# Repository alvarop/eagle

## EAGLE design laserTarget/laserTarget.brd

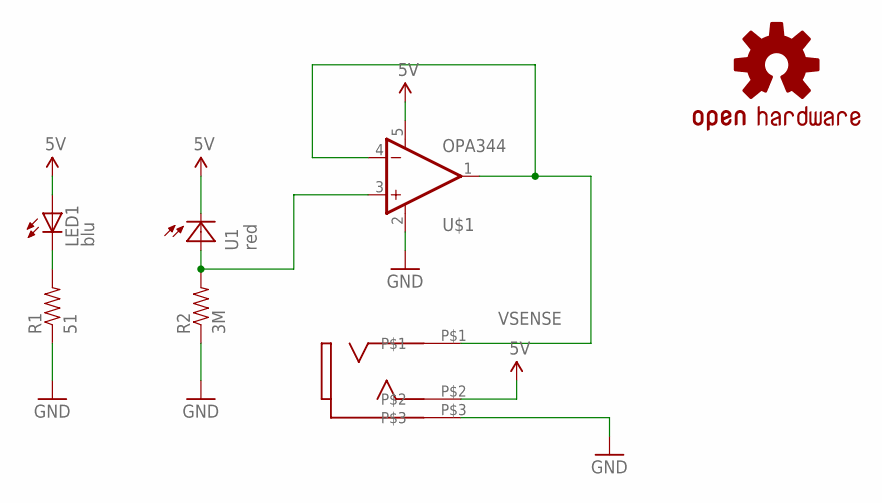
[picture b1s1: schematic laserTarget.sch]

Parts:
LED1: blu; LED5MM
LOGO1: OSHW-LOGOS; OSHW-LOGO-S
R1: 51; 0805
R2: 3M; 0805
U1: red; CLS15
U$1: OPA344; SOT23-5
U$2: 35RASMT2BHNTRX

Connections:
5V: LED1.A, U1.3 (C), U1.4 (C), U$1.5 (V+), U$2.P$2
GND: R1.1, R2.1, U$1.2 (V-), U$2.P$3
unnamed: R2.2, U1.1 (A), U1.2 (A), U$1.3 (+IN)
unnamed: LED1.K (C), R1.2
VSENSE: U$1.1 (OUT), U$1.4 (-IN), U$2.P$1

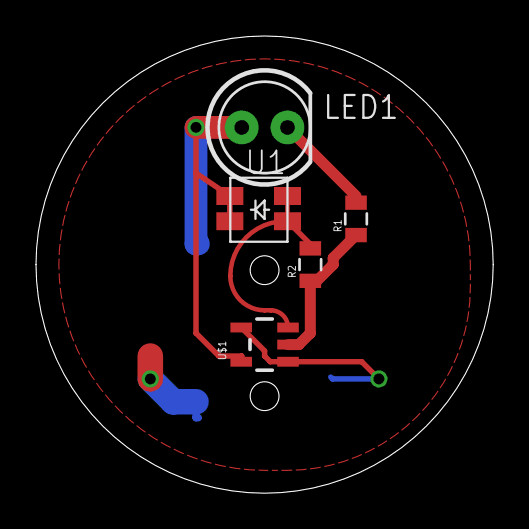
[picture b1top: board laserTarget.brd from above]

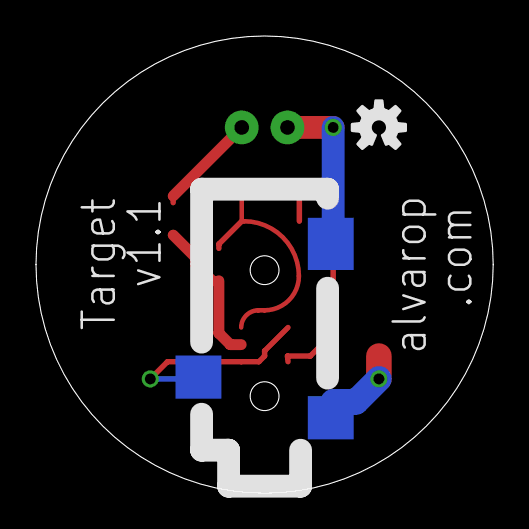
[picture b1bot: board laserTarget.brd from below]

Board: 2 copper layers, 25.4 x 25.4 mm, 7 parts (2 on the bottom side), 5 nets.

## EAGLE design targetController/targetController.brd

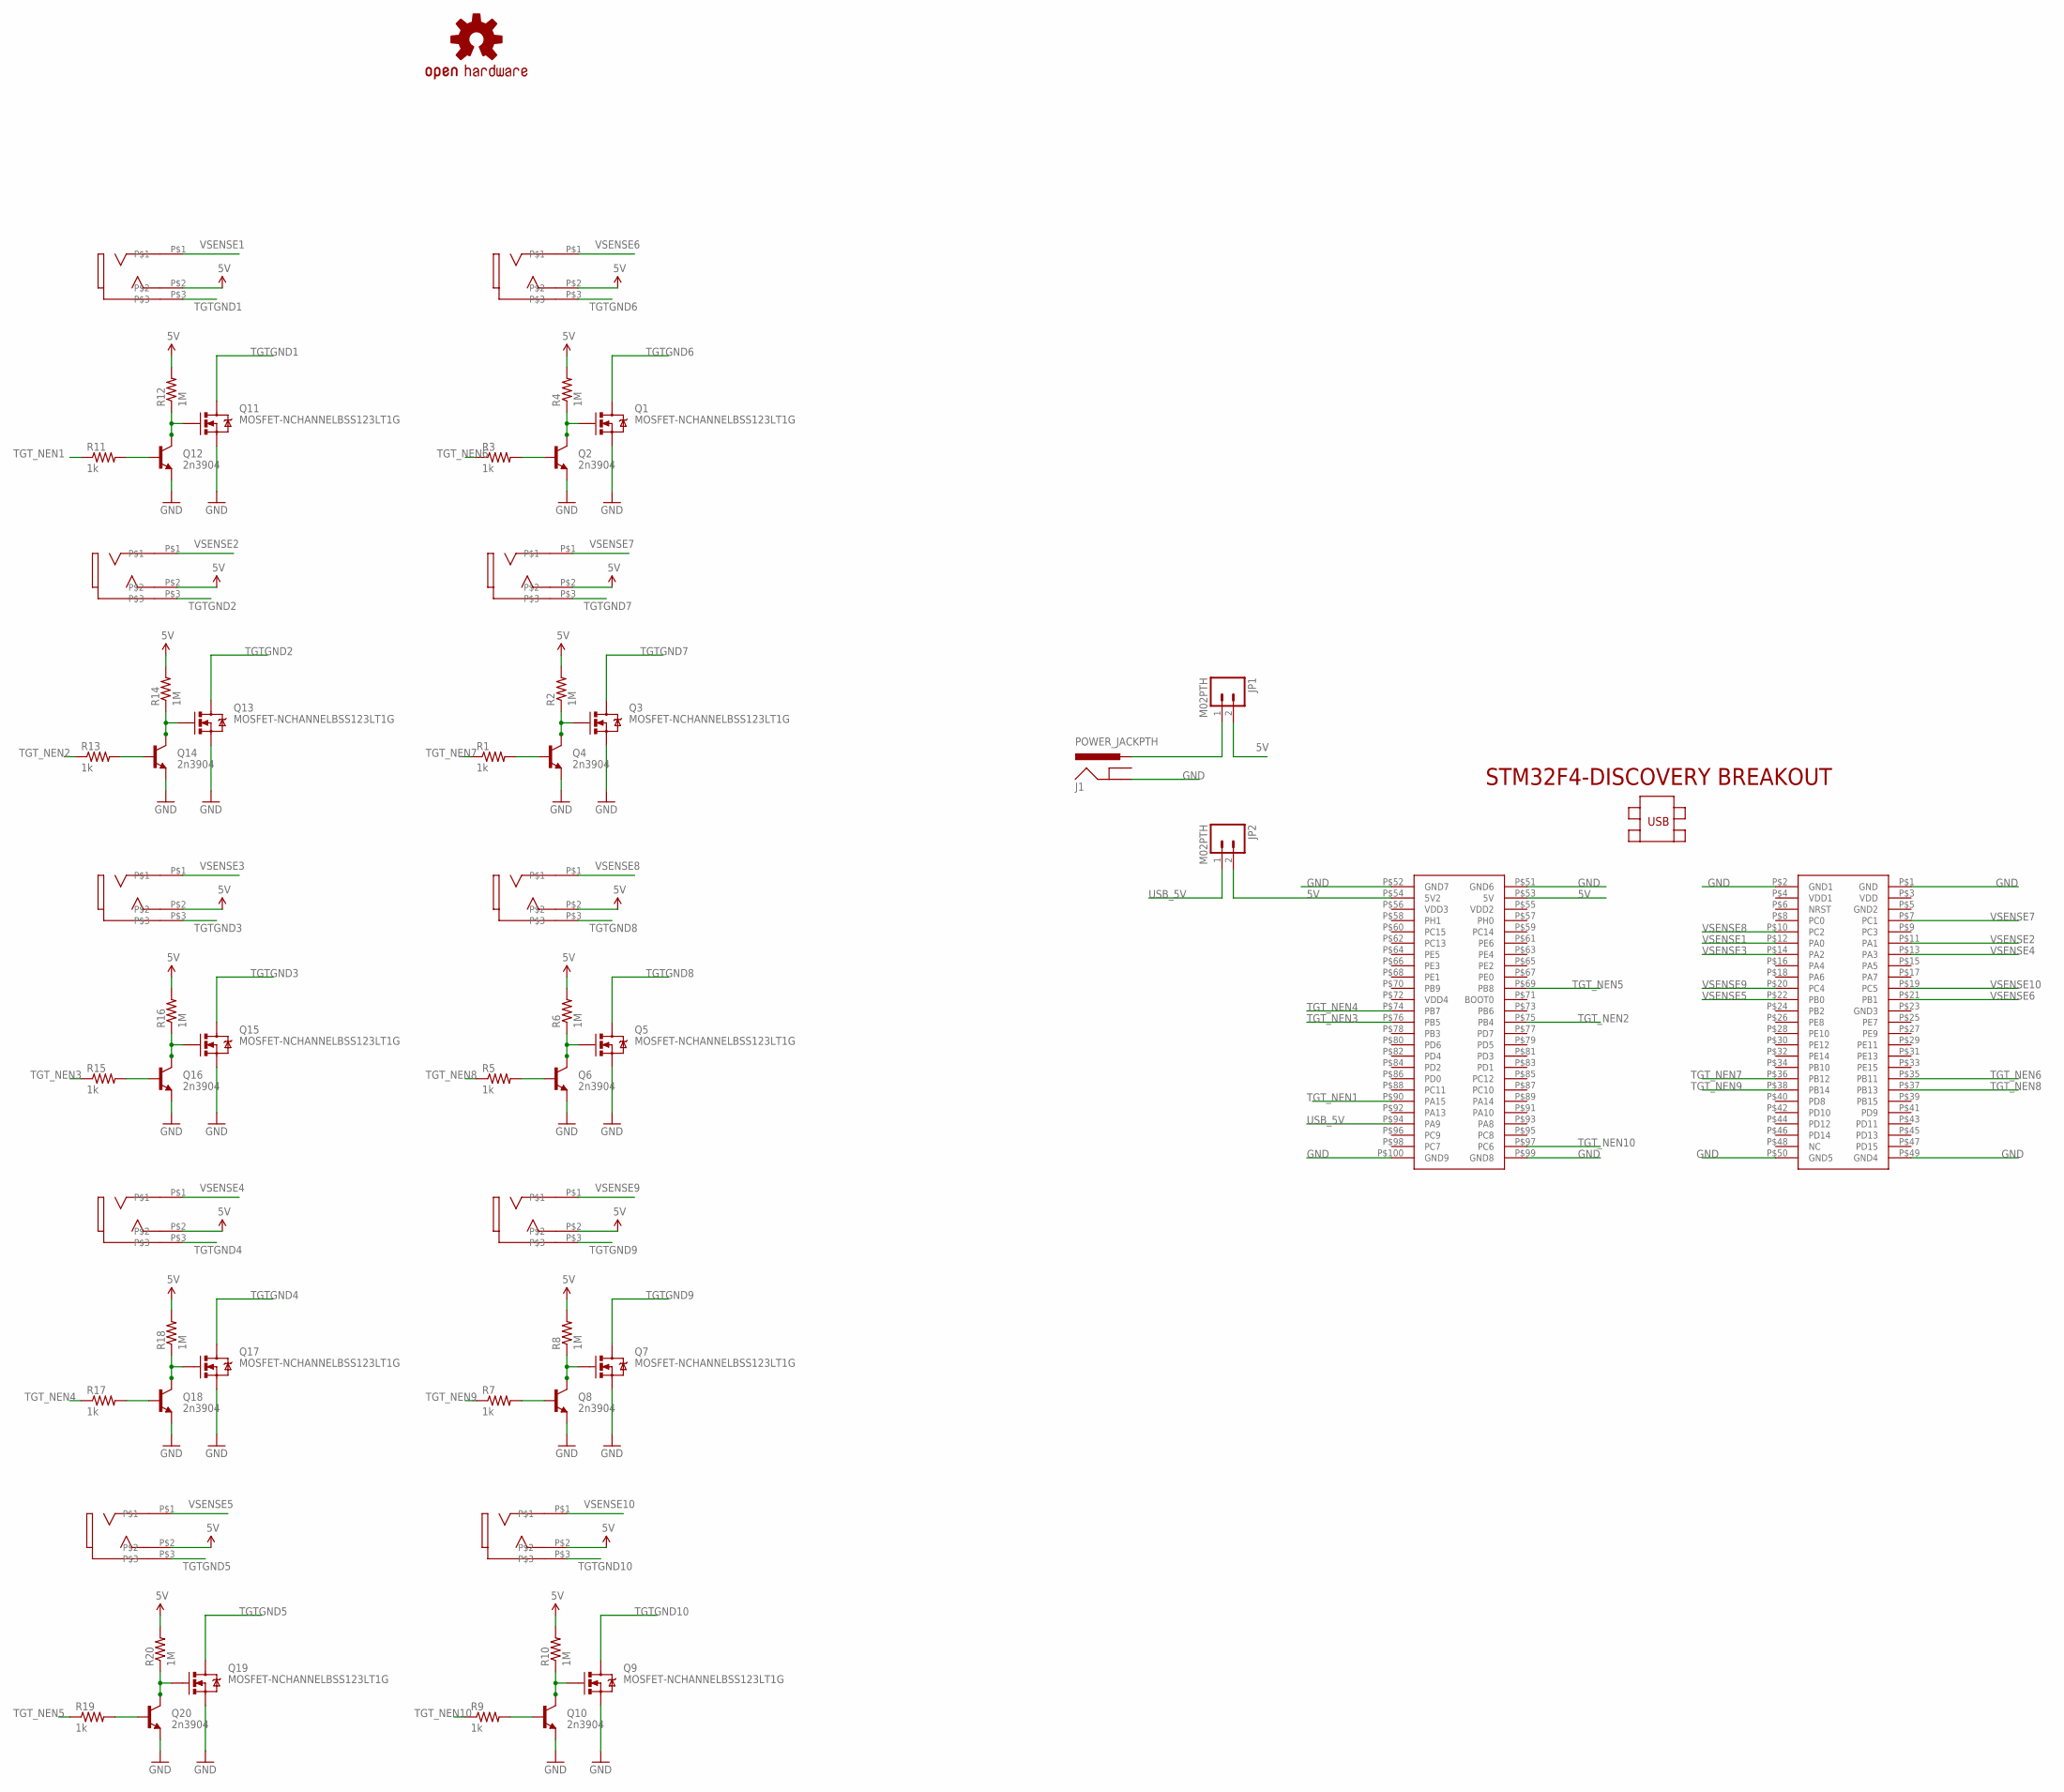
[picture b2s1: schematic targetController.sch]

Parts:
J1: POWER_JACKPTH; POWER_JACK_PTH
JP1, JP2: M02PTH; 1X02
LOGO1: OSHW-LOGOS; OSHW-LOGO-S
Q1, Q3, Q5, Q7, Q9, Q11, Q13, Q15, Q17, Q19: MOSFET-NCHANNELBSS123LT1G; SOT23
Q2, Q4, Q6, Q8, Q10, Q12, Q14, Q16, Q18, Q20: 2n3904; SOT23-3
R1, R3, R5, R7, R9, R11, R13, R15, R17, R19: 1k; 0805
R2, R4, R6, R8, R10, R12, R14, R16, R18, R20: 1M; 0805
T1, T2, T3, T4, T5, T6, T7, T8, T9, T10: 35RASMT2BHNTRX
U$1: STM32F4-DISCOVERY

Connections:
5V: JP1.2, JP2.2, R2.2, R4.2, R6.2, R8.2, R10.2, R12.2, R14.2, R16.2, R18.2, R20.2, T1.P$2, T2.P$2, T3.P$2, T4.P$2, T5.P$2, T6.P$2, T7.P$2, T8.P$2, T9.P$2, T10.P$2, U$1.P$53 (5V), U$1.P$54 (5V2)
GND: J1.GND, Q1.2 (S), Q2.2 (E), Q3.2 (S), Q4.2 (E), Q5.2 (S), Q6.2 (E), Q7.2 (S), Q8.2 (E), Q9.2 (S), Q10.2 (E), Q11.2 (S), Q12.2 (E), Q13.2 (S), Q14.2 (E), Q15.2 (S), Q16.2 (E), Q17.2 (S), Q18.2 (E), Q19.2 (S), Q20.2 (E), U$1.P$1 (GND), U$1.P$2 (GND1), U$1.P$49 (GND4), U$1.P$50 (GND5), U$1.P$51 (GND6), U$1.P$52 (GND7), U$1.P$99 (GND8), U$1.P$100 (GND9)
N1: Q3.1 (G), Q4.3 (C), R2.1
N2: Q5.1 (G), Q6.3 (C), R6.1
N3: Q1.1 (G), Q2.3 (C), R4.1
N4: Q7.1 (G), Q8.3 (C), R8.1
N5: Q9.1 (G), Q10.3 (C), R10.1
N6: Q11.1 (G), Q12.3 (C), R12.1
N7: Q13.1 (G), Q14.3 (C), R14.1
N8: Q15.1 (G), Q16.3 (C), R16.1
N9: Q17.1 (G), Q18.3 (C), R18.1
N10: Q19.1 (G), Q20.3 (C), R20.1
unnamed: Q4.1 (B), R1.2
unnamed: J1.PWR, JP1.1
unnamed: Q2.1 (B), R3.2
unnamed: Q6.1 (B), R5.2
unnamed: Q8.1 (B), R7.2
unnamed: Q10.1 (B), R9.2
unnamed: Q12.1 (B), R11.2
unnamed: Q14.1 (B), R13.2
unnamed: Q16.1 (B), R15.2
unnamed: Q18.1 (B), R17.2
unnamed: Q20.1 (B), R19.2
TGTGND1: Q11.3 (D), T1.P$3
TGTGND2: Q13.3 (D), T2.P$3
TGTGND3: Q15.3 (D), T3.P$3
TGTGND4: Q17.3 (D), T4.P$3
TGTGND5: Q19.3 (D), T5.P$3
TGTGND6: Q1.3 (D), T6.P$3
TGTGND7: Q3.3 (D), T7.P$3
TGTGND8: Q5.3 (D), T8.P$3
TGTGND9: Q7.3 (D), T9.P$3
TGTGND10: Q9.3 (D), T10.P$3
TGT_NEN1: R11.1, U$1.P$90 (PA15)
TGT_NEN2: R13.1, U$1.P$75 (PB4)
TGT_NEN3: R15.1, U$1.P$76 (PB5)
TGT_NEN4: R17.1, U$1.P$74 (PB7)
TGT_NEN5: R19.1, U$1.P$69 (PB8)
TGT_NEN6: R3.1, U$1.P$35 (PB11)
TGT_NEN7: R1.1, U$1.P$36 (PB12)
TGT_NEN8: R5.1, U$1.P$37 (PB13)
TGT_NEN9: R7.1, U$1.P$38 (PB14)
TGT_NEN10: R9.1, U$1.P$97 (PC6)
USB_5V: JP2.1, U$1.P$94 (PA9)
VSENSE1: T1.P$1, U$1.P$12 (PA0)
VSENSE2: T2.P$1, U$1.P$11 (PA1)
VSENSE3: T3.P$1, U$1.P$14 (PA2)
VSENSE4: T4.P$1, U$1.P$13 (PA3)
VSENSE5: T5.P$1, U$1.P$22 (PB0)
VSENSE6: T6.P$1, U$1.P$21 (PB1)
VSENSE7: T7.P$1, U$1.P$7 (PC1)
VSENSE8: T8.P$1, U$1.P$10 (PC2)
VSENSE9: T9.P$1, U$1.P$20 (PC4)
VSENSE10: T10.P$1, U$1.P$19 (PC5)

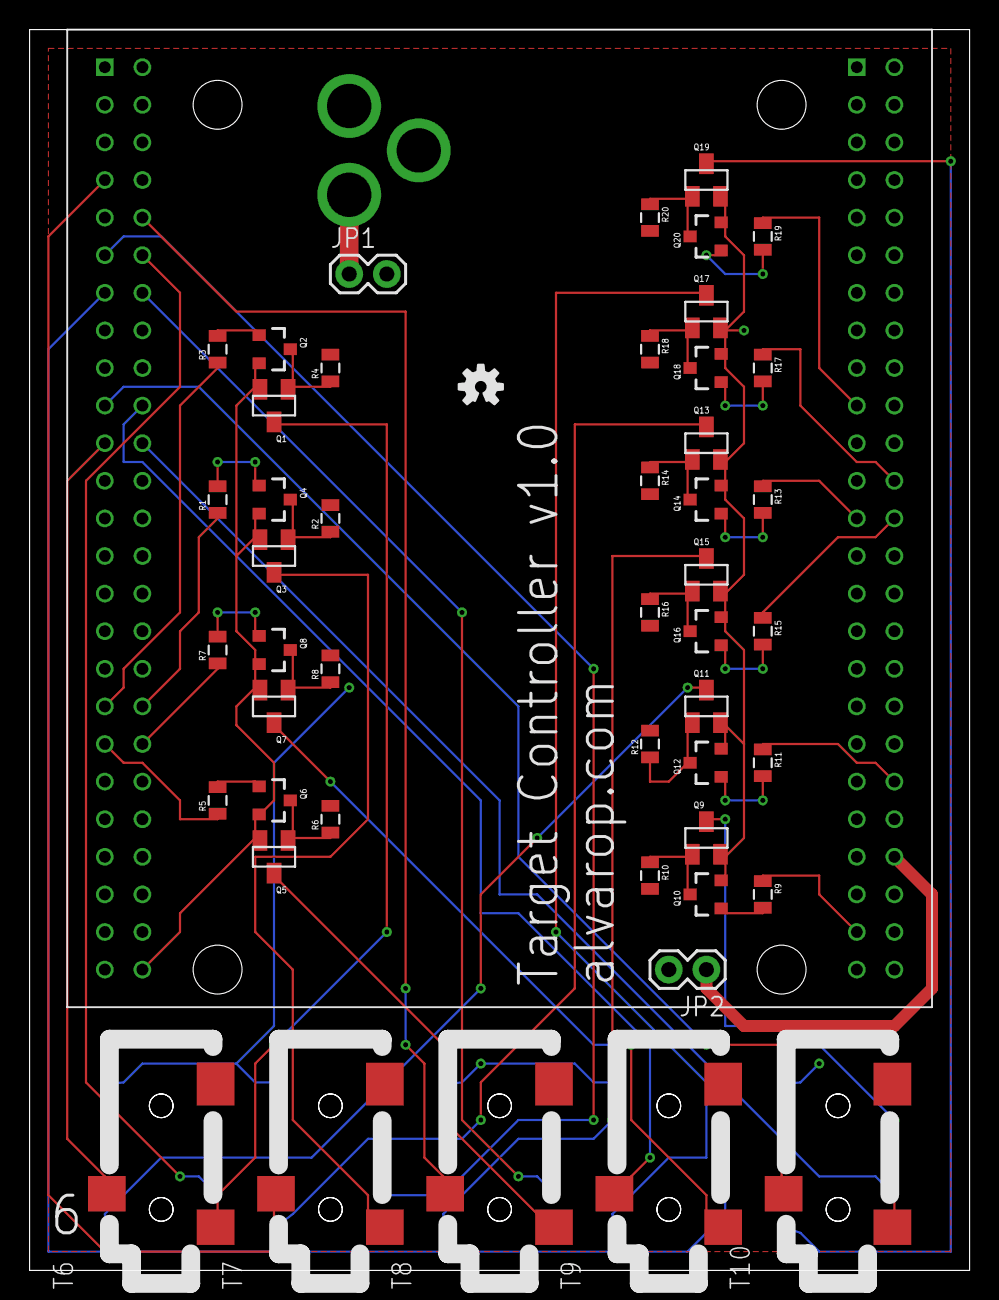
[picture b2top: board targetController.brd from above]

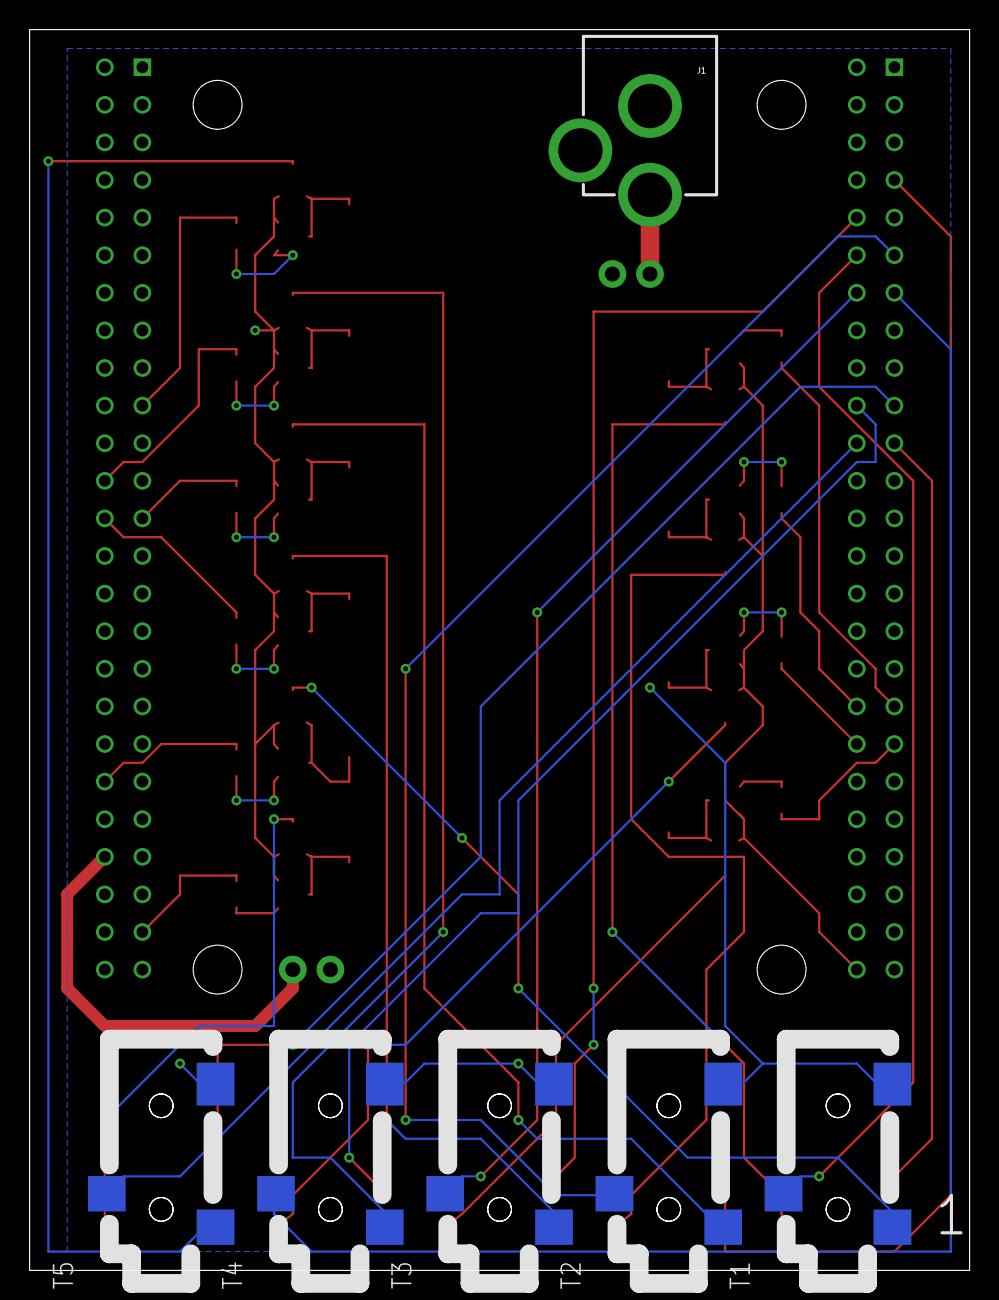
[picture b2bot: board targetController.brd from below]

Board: 2 copper layers, 63.5 x 83.8 mm, 59 parts (6 on the bottom side), 54 nets.

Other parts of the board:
U$2, U$3, U$4, U$5: STAND-OFF

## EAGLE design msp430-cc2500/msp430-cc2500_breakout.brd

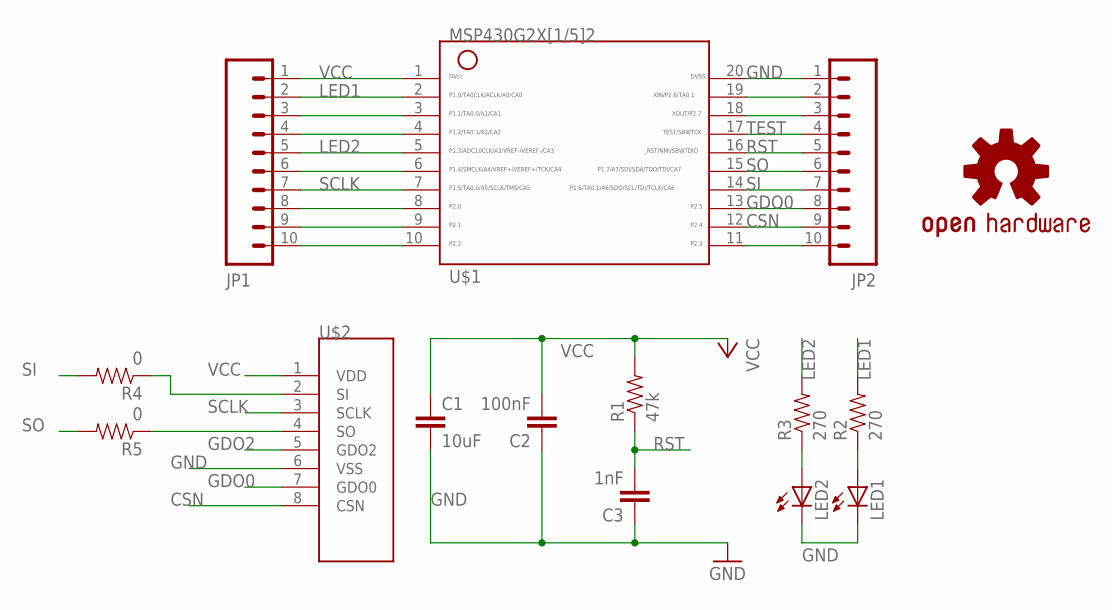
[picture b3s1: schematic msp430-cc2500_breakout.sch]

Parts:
C1: 10uF; 0805
C2: 100nF; 0805
C3: 1nF; 0805
JP1, JP2: M10"; 1X10
LED1, LED2: LED1206; LED-1206
R1: 47k; 0805
R2, R3: 270; 0805
R4, R5: 0; 0805
U$1: G2X[1/5]2---PW20; PW20
U$2: CC2500-MODULESMT; CC2500-MODULE-SMT
U$3: OSHW-LOGOL; OSHW-LOGO-L

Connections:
CSN: JP2.9, U$1.12, U$2.8 (CSN)
GDO0: JP2.8, U$1.13, U$2.7 (GDO0)
GDO2: U$2.5 (GDO2)
GND: C1.2, C2.1, C3.1, JP2.1, LED1.C, LED2.C, U$1.20, U$2.6 (VSS)
LED1: JP1.2, R2.2, U$1.2
LED2: JP1.5, R3.2, U$1.5
unnamed: LED1.A, R2.1
unnamed: JP1.3, U$1.3
unnamed: JP1.4, U$1.4
unnamed: JP1.6, U$1.6
unnamed: LED2.A, R3.1
unnamed: JP1.8, U$1.8
unnamed: JP1.9, U$1.9
unnamed: JP1.10, U$1.10
unnamed: JP2.2, U$1.19
unnamed: JP2.3, U$1.18
unnamed: JP2.10, U$1.11
unnamed: R4.1, U$2.2 (SI)
unnamed: R5.1, U$2.4 (SO)
RST: C3.2, JP2.5, R1.1, U$1.16
SCLK: JP1.7, U$1.7, U$2.3 (SCLK)
SI: JP2.7, R4.2, U$1.14
SO: JP2.6, R5.2, U$1.15
TEST: JP2.4, U$1.17
VCC: C1.1, C2.2, JP1.1, R1.2, U$1.1, U$2.1 (VDD)

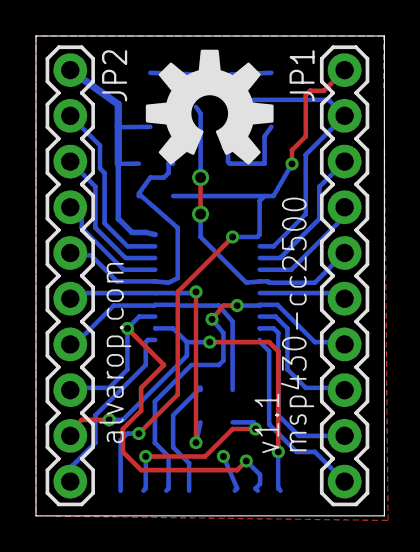
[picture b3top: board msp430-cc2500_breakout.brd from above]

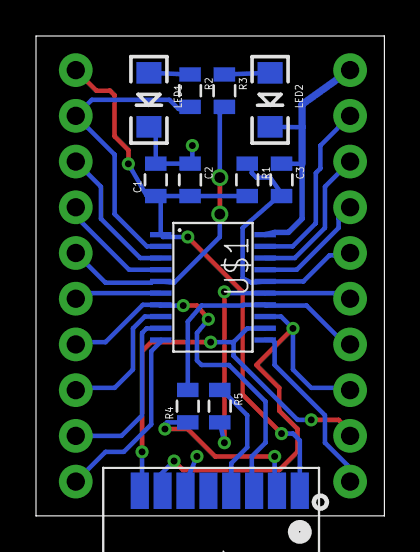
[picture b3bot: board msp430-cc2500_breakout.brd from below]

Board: 2 copper layers, 19.4 x 26.7 mm, 15 parts (12 on the bottom side), 24 nets.

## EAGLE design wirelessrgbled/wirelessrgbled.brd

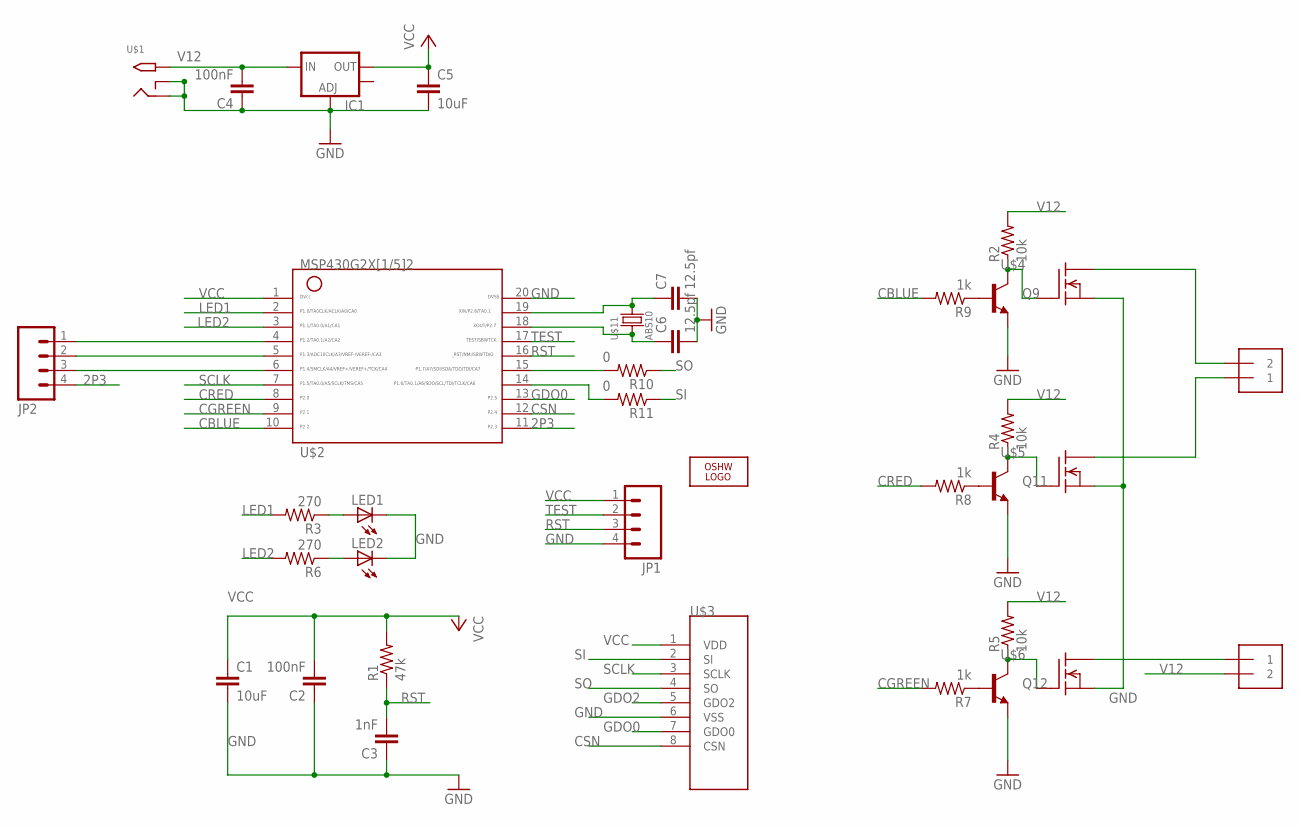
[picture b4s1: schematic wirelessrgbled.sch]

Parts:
C1, C5: 10uF; 0805
C2, C4: 100nF; 0805
C3: 1nF; 0805
C6, C7: 12.5pf; 0805
IC1: V_REG_LM1117SOT223; SOT223
J1, J2: 1X2-3.5MM
JP1, JP2: M04PTH; 1X04
LED1, LED2: LEDCHIPLED_0805; CHIPLED_0805
LOGO1: OSHW_LOGO_10MILX0200-NT; OSHW_10X200_NOTEXT
Q9, Q11, Q12: TRANSISTOR_NPNSOT23; SOT23
R1: 47k; 0805
R2, R4, R5: 10k; 0805
R3, R6: 270; 0805
R7, R8, R9: 1k; 0805
R10, R11: 0; 0805
U$1: 2.1MMJACKTHM; PJ-102A
U$2: G2X[1/5]2---PW20; PW20
U$3: CC2500-MODULE
U$4, U$5, U$6: BUK92150; TO252
U$11: ABS10

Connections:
2P3: JP2.4, U$2.11
CBLUE: R9.2, U$2.10
CGREEN: R7.2, U$2.9
CRED: R8.2, U$2.8
CSN: U$2.12, U$3.8 (CSN)
GDO0: U$2.13, U$3.7 (GDO0)
GDO2: U$3.5 (GDO2)
GND: C1.2, C2.1, C3.1, C4.1, C5.2, C6.2, C7.2, IC1.1 (ADJ), JP1.4, LED1.C, LED2.C, Q9.2 (E), Q11.2 (E), Q12.2 (E), U$1.RING, U$1.RING_SW, U$2.20, U$3.6 (VSS), U$4.3 (S), U$5.3 (S), U$6.3 (S)
LED1: R3.2, U$2.2
LED2: R6.2, U$2.3
unnamed: JP2.2, U$2.5
unnamed: Q9.3 (C), R2.1, U$4.1 (G)
unnamed: LED1.A, R3.1
unnamed: J2.1, U$6.2 (D)
unnamed: J1.2, U$4.2 (D)
unnamed: J1.1, U$5.2 (D)
unnamed: R10.2, U$2.15
unnamed: LED2.A, R6.1
unnamed: R11.2, U$2.14
unnamed: Q11.3 (C), R4.1, U$5.1 (G)
unnamed: Q9.1 (B), R9.1
unnamed: Q11.1 (B), R8.1
unnamed: Q12.1 (B), R7.1
unnamed: Q12.3 (C), R5.1, U$6.1 (G)
unnamed: JP2.1, U$2.4
unnamed: JP2.3, U$2.6
unnamed: C7.1, U$2.19, U$11.P$2
unnamed: C6.1, U$2.18, U$11.P$1
RST: C3.2, JP1.3, R1.1, U$2.16
SCLK: U$2.7, U$3.3 (SCLK)
SI: R11.1, U$3.2 (SI)
SO: R10.1, U$3.4 (SO)
TEST: JP1.2, U$2.17
V12: C4.2, IC1.3 (IN), J2.2, R2.2, R4.2, R5.2, U$1.TIP
VCC: C1.1, C2.2, C5.1, IC1.2 (OUT), JP1.1, R1.2, U$2.1, U$3.1 (VDD)

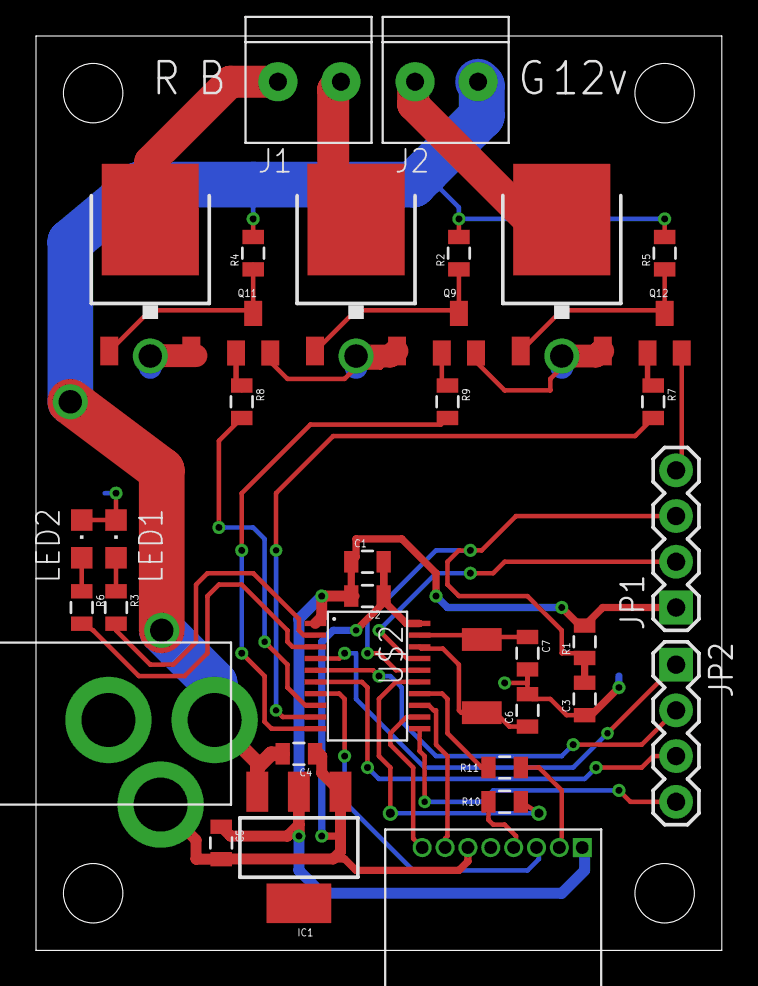
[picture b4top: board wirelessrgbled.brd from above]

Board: 2 copper layers, 38.1 x 50.8 mm, 40 parts (1 on the bottom side), 34 nets.

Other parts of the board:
U$7, U$8, U$9, U$10: STAND-OFF

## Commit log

2012-05-03 Adding wirelessrgbled
2012-05-25 Updating wirelessrgbled to v1.1
    Adding msp430-cc2500 v1.1
2014-03-09 Adding my lib
2014-03-09 First commit of laserTarget
2014-03-09 Stupid. Sensor output not connected (was connected to 5V instead...)
2014-03-10 Starting targetController
2014-03-10 Routed targetController
2014-03-10 Removed test stuff from target

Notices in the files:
parts and their libraries:
SparkFun-LED: Licensing: CC v3.0 Share-Alike You are welcome to use this library for commercial purposes.
